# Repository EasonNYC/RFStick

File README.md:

# RFStick
A small IoT PCB for the Atmega 328p with Lipo charger and Battery Gas Gauge with an on-board 2.4GHz RF transceiver.

Author: Eason Smith (Eason@EasonRobotics.com)

Written with Cadsoft Eagle v7.2

This project is currently in developement. 

For more project details please visit: http://www.easonrobotics.com/?portfolio=rf-stick

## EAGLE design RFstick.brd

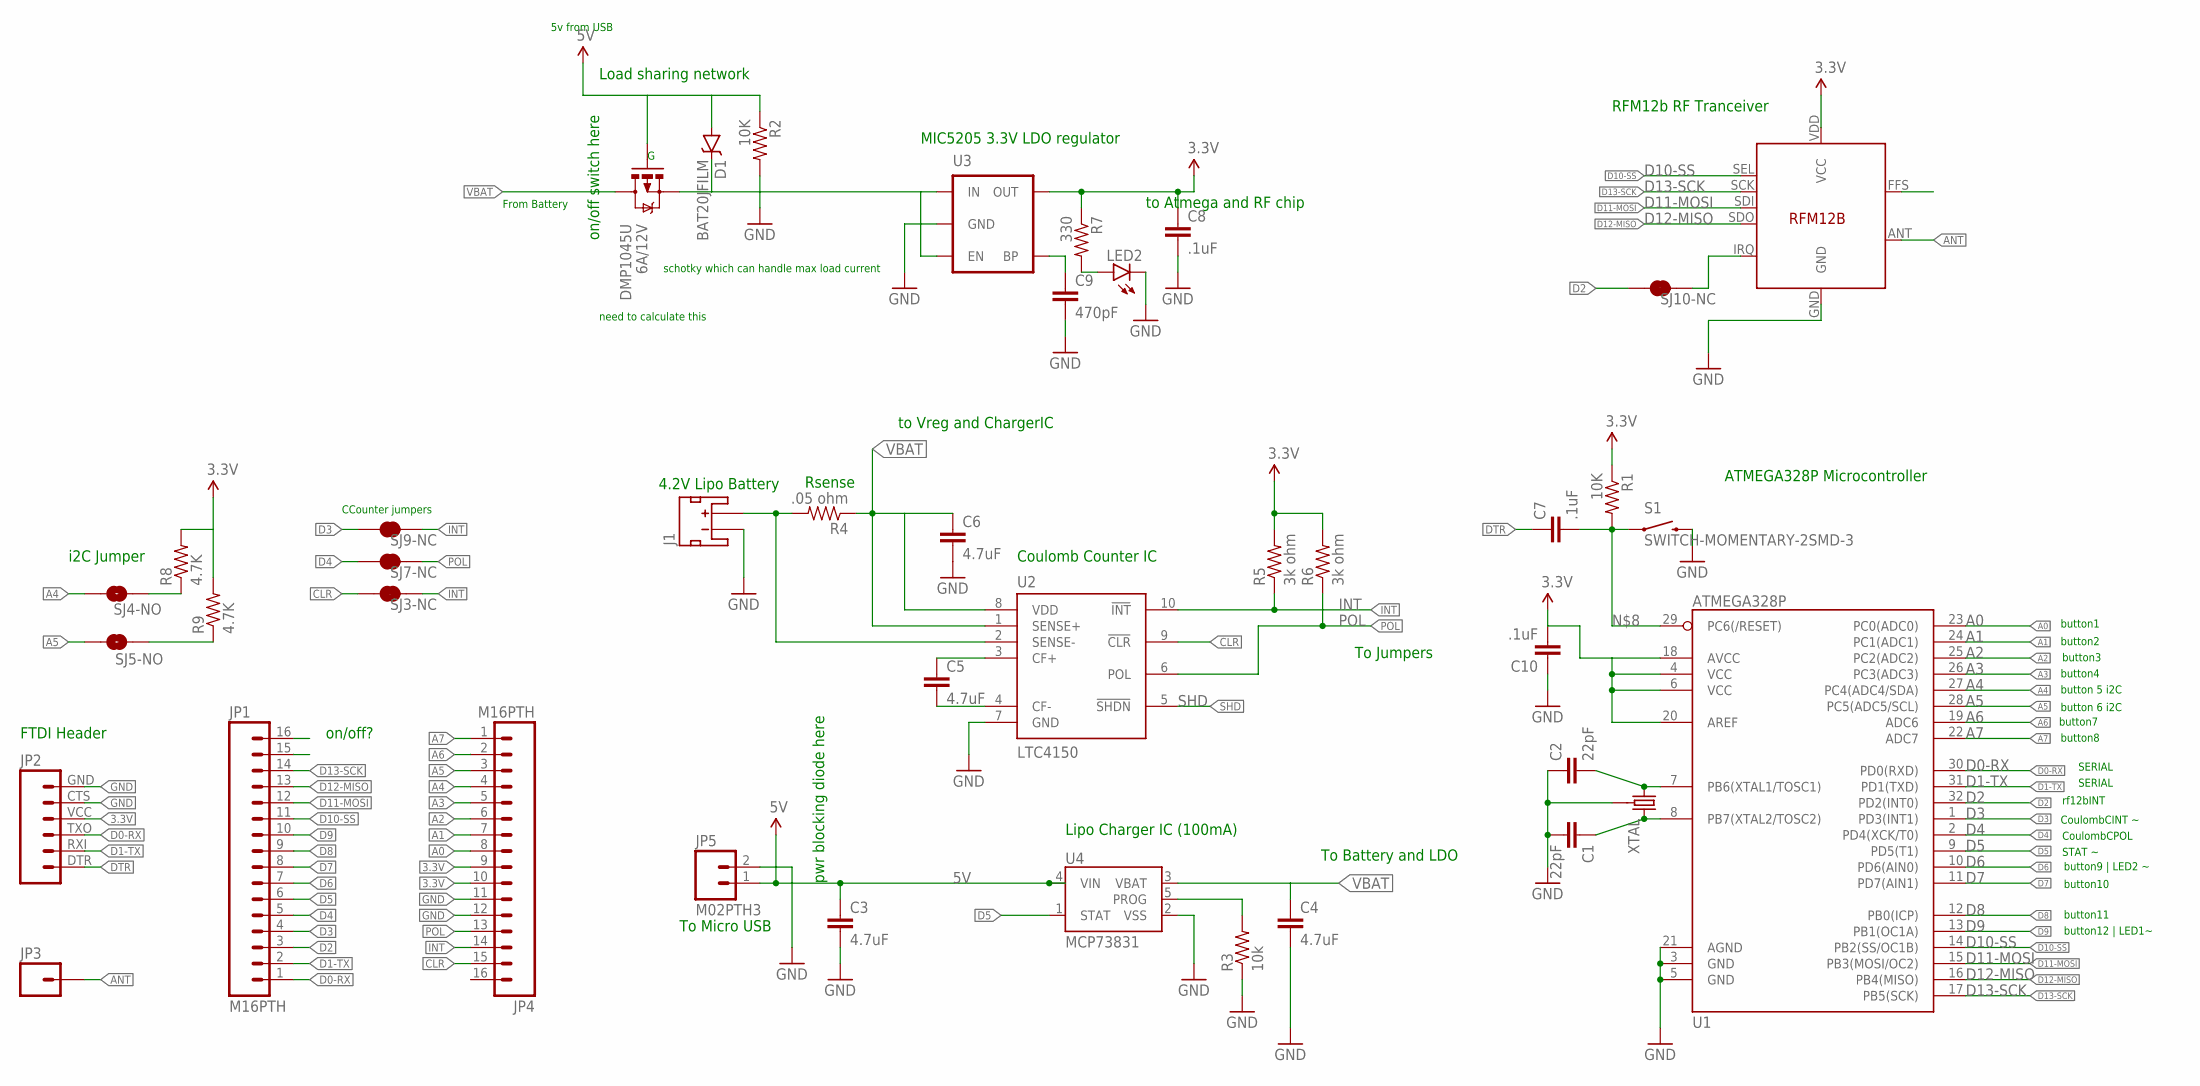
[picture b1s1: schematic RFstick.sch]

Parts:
C1, C2: 22pF; 0603-CAP; MPN 04025A220JAT2A
C3, C4, C5, C6: 4.7uF; 0603-CAP; MPN F981A475MMA
C7, C8, C10: .1uF; 0603-CAP; MPN MC0603B104M500CT
C9: 470pF; 0603-CAP; MPN 06031C471JAT2A
D1: BAT20JFILM; SOD-323
DMP1045U: 6A/12V; SOT23-3
J1: JST_2MM_MALE; JST-2-SMD
JP1, JP4: M16PTH; 1X16
JP2: M06SIP; 1X06
JP3: M01PTH; 1X01
JP5: M02PTH3; 1X02_LONGPADS
LED2: LED0603; LED-0603; MPN 150060RS75000
R1, R2: 10K; 0603-RES; MPN CRCW060310K0FKEAHP
R3: 10k; 0603-RES; MPN CRCW06032K00FKEA
R4: .05 ohm; 0603-RES; MPN MC0063W060311R0
R5, R6: 3k ohm; 0603-RES; MPN SR1-0603-230
R7: 330; 0603-RES
R8, R9: 4.7K; 0603-RES; MPN CRCW06034K70FKEA
S1: SWITCH-MOMENTARY-2SMD-3; TACTILE_SWITCH_SMD-3
SJ3-NC, SJ7-NC, SJ9-NC, SJ10-NC: JUMPER-PAD-2-NC_BY_TRACENO_SILK; PAD-JUMPER-2-NC_BY_TRACE_NO_SILK
SJ4-NO, SJ5-NO: JUMPER-PAD-2-NO; PAD-JUMPER-2-NO_NO_SILK
U1: ATMEGA328P; TQFP32-08
U2: LTC4150; MSOP10; MPN LTC4150CMS#PBF
U3: MIC52053.3V; SOT23-5; MPN MIC5205-3.3YM5 TR
U4: MCP73831; SOT23-5; MPN MCP73831T-2ACI/OT
U$1: XTAL; CRYSTAL-SMD-5X3; MPN AA-16.000MALE-T
U$2: RFM12B

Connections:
3.3V: C8.1, C10.2, JP2.VCC (4), JP4.9, JP4.10, R1.1, R5.2, R6.2, R7.1, R8.2, R9.2, U1.4 (VCC), U1.6 (VCC), U1.18 (AVCC), U1.20 (AREF), U3.5 (OUT), U$2.VDD (VCC)
5V: C3.1, D1.A, DMP1045U.1 (G), JP5.1, R2.1, U4.4 (VIN)
A0: JP4.8, U1.23 (PC0(ADC0))
A1: JP4.7, U1.24 (PC1(ADC1))
A2: JP4.6, U1.25 (PC2(ADC2))
A3: JP4.5, U1.26 (PC3(ADC3))
A4: JP4.4, SJ4-NO.1, U1.27 (PC4(ADC4/SDA))
A5: JP4.3, SJ5-NO.1, U1.28 (PC5(ADC5/SCL))
A6: JP4.2, U1.19 (ADC6)
A7: JP4.1, U1.22 (ADC7)
ANT: JP3.1, U$2.ANT
CLR: JP4.15, SJ3-NC.1, U2.9 (!CLR!)
D0-RX: JP1.1, JP2.TXO (3), U1.30 (PD0(RXD))
D1-TX: JP1.2, JP2.RXI (2), U1.31 (PD1(TXD))
D2: JP1.3, SJ10-NC.1, U1.32 (PD2(INT0))
D3: JP1.4, SJ9-NC.1, U1.1 (PD3(INT1))
D4: JP1.5, SJ7-NC.1, U1.2 (PD4(XCK/T0))
D5: JP1.6, U1.9 (PD5(T1)), U4.1 (STAT)
D6: JP1.7, U1.10 (PD6(AIN0))
D7: JP1.8, U1.11 (PD7(AIN1))
D8: JP1.9, U1.12 (PB0(ICP))
D9: JP1.10, U1.13 (PB1(OC1A))
D10-SS: JP1.11, U1.14 (PB2(SS/OC1B)), U$2.SEL
D11-MOSI: JP1.12, U1.15 (PB3(MOSI/OC2)), U$2.SDI
D12-MISO: JP1.13, U1.16 (PB4(MISO)), U$2.SDO
D13-SCK: JP1.14, U1.17 (PB5(SCK)), U$2.SCK
DTR: C7.1, JP2.DTR (1)
GND: C1.2, C2.1, C3.2, C4.2, C6.2, C8.2, C9.2, C10.1, J1.1 (-), JP2.CTS (5), JP2.GND (6), JP4.11, JP4.12, JP5.2, LED2.C, R2.2, R3.1, S1.4 (2), U1.3 (GND), U1.5 (GND), U1.21 (AGND), U2.7 (GND), U3.2 (GND), U4.2 (VSS), U$1.2 (3), U$1.4 (3), U$2.GND
INT: JP4.14, R5.1, SJ3-NC.2, SJ9-NC.2, U2.10 (!INT!)
unnamed: C1.1, U1.8 (PB7(XTAL2/TOSC2)), U$1.1 (2)
unnamed: C2.2, U1.7 (PB6(XTAL1/TOSC1)), U$1.3 (1)
unnamed: R3.2, U4.5 (PROG)
unnamed: C5.1, U2.3 (CF+)
unnamed: LED2.A, R7.2
unnamed: C7.2, R1.2, S1.1, U1.29 (PC6(/RESET))
unnamed: C5.2, U2.4 (CF-)
unnamed: J1.2 (+), R4.2, U2.2 (SENSE-)
unnamed: C9.1, U3.4 (BP)
unnamed: R8.1, SJ4-NO.2
unnamed: R9.1, SJ5-NO.2
unnamed: D1.C, DMP1045U.2 (S), U3.1 (IN), U3.3 (EN)
unnamed: SJ10-NC.2, U$2.IRQ
POL: JP4.13, R6.1, SJ7-NC.2, U2.6 (POL)
SHD: U2.5 (!SHDN!)
VBAT: C4.1, C6.1, DMP1045U.3 (D), R4.1, U2.1 (SENSE+), U2.8 (VDD), U4.3 (VBAT)

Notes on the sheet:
MIC5205 3.3V LDO regulator
Coulomb Counter IC
Lipo Charger IC (100mA)
To Micro USB
4.2V Lipo Battery
to Vreg and ChargerIC
to Atmega and RF chip
pwr blocking diode here
Rsense
i2C Jumper
FTDI Header
To Battery and LDO
rf12bINT
CoulombCINT ~
CCounter jumpers
button 5 i2C
button 6 i2C
SERIAL
CoulombCPOL
STAT ~
button9 | LED2 ~
button10
button11
button12 | LED1~
button1
button2
button3
button4
button7
button8
To Jumpers
From Battery
5v from USB
schotky which can handle max load current
Load sharing network
need to calculate this
RFM12b RF Tranceiver
ATMEGA328P Microcontroller
on/off switch here
on/off?

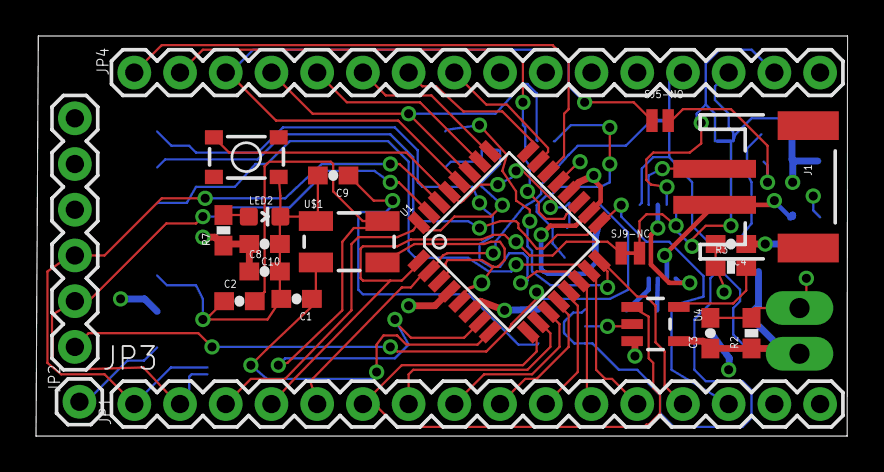
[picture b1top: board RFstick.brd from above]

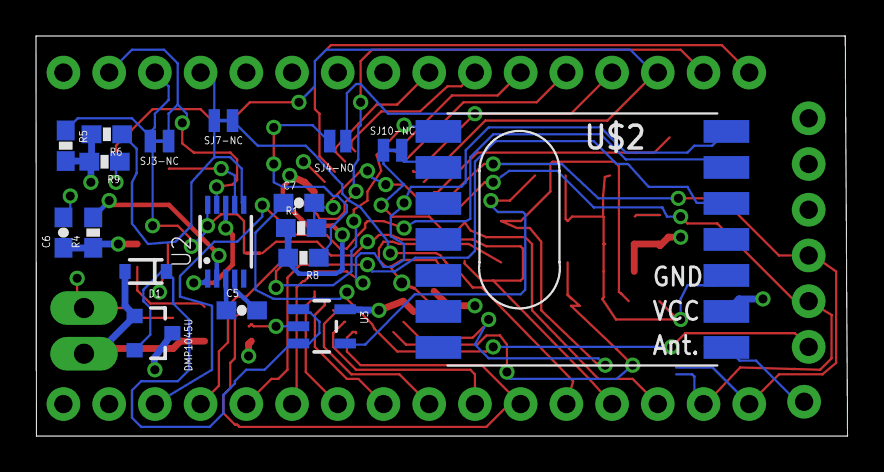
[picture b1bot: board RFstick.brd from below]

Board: 4 copper layers, 45.1 x 22.2 mm, 41 parts (18 on the bottom side), 44 nets.

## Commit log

2016-02-08 initial files upload

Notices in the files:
parts and their libraries:
SparkFun-DigitalIC: Licensing: Creative Commons ShareAlike 4.0 International - https://creativecommons.org/licenses/by-sa/4.0
